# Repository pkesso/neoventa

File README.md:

# Neoventa — Venta Overdrive PCB

A PCB for the Venta Overdrive, a clone of the PE-12 overdrive by Elektronika. The board is 50 × 54 mm, has 2 layers and fits a Hammond 1590N1 (125B) enclosure. SMD parts go on the bottom side and are assembled by JLCPCB. Pots and the wire pads go on the top side and are soldered by hand.

The schematic and the board are generated by Python scripts from a single circuit description (`tools/circuit2.py`). The layout was not drawn by hand in KiCad.

## Status

**Done**
- The schematic was traced from the stripboard layout and checked against the factory schematic of the PE-12 (`pics/moar/1.png`, `2.png`).
- The ngspice simulation gives about ±0.25 V at the output for a 100 mV, 440 Hz input at Volume 50% (see `simulations/`).
- The board is placed and routed by the scripts. The scripts' own DRC (`tools/drc.py`) reports 0 violations.
- The JLCPCB BOM and CPL files are generated (`jlcpcb/`).
- There is a drilling template for the enclosure lid.

**To do**
- Fill the GND zones (press **B** in the PCB editor), then run KiCad's DRC (Inspect → Design Rules Checker).
- Export Gerbers and drill files (File → Fabrication Outputs).
- Check the orientation of the SOIC-8 and the diodes in the JLCPCB assembly preview. The assembly side is **Bottom**.
- Add 3D models for the pots. The footprints in `Venta.pretty/` don't have any yet.

## Repository layout

```
venta_overdrive.kicad_pro     KiCad project
venta_overdrive.kicad_sch     Schematic (generated by tools/gen_sch2.py)
venta_overdrive.kicad_pcb     Board (generated by tools/write_pcb.py)
Venta.kicad_sym               Project symbol library
Venta.pretty/                 Project footprints: Alpha 16 mm RA pots (single/dual), wire pad
fp-lib-table, sym-lib-table   Library tables (paths relative to ${KIPRJMOD})
jlcpcb/                       BOM_JLCPCB.csv, CPL_JLCPCB.csv for JLCPCB assembly
simulations/                  venta.lib (SPICE models), simulate.py and the plots it generates
drill_template_1590N1.pdf     Lid drilling template, print at 100 % scale (generated by tools/drill_template.py)
tools/                        Python scripts that generate the schematic and the board
requirements.txt              Python dependencies for tools/
```

## Hardware

- **Enclosure:** Hammond 1590N1 (66.5 × 122 × 39.5 mm).
- **Knobs:** 2 × 2. Volume and Drive on top, Eq and Resonance below. IN/OUT jacks on the sides, power on the top.
- **Pots:** Alpha 16 mm, right-angle PCB mount ("41" terminals), B50k: RV16AF-41 single, RV16A01F-41 dual for Eq. The footprints follow the [Alpha datasheet](https://cdn-blog.adafruit.com/uploads/2022/01/Taiwan-Alpha-16mm-pots-datasheet.pdf) (pages 43–45): body Ø17, pin rows 16 mm (and 11 mm on the dual) from the shaft, 5 mm pitch.
- **Board height:** the board sits **12 mm** behind the pots' mounting surface (the inside of the lid, where the bushings rest). The dual pot body is 11.5 mm deep (singles 9.1 mm), and the pins are long enough for up to about 13 mm, so all four bushings are flush with the lid only in the 11.5–13 mm window.
- **Op-amps:** 4558 (JRC4558D, LCSC C443686).
- **Footswitch:** 3PDT, wired to the board.
- **Status LED:** external, with its own resistor. Anode to J6 (LED+), cathode to a 3PDT lug; the common of that 3PDT pole goes to J7 (GND), so the LED lights when the effect is on.
- **Wire pads:** J1 IN, J2 OUT, J3 +9V, J4/J5 GND, J6 LED+ (VCC, to the LED anode), J7 GND (to the 3PDT LED pole).

### Power: DC jack or 9 V battery

The board takes power from J3 (+9V) and J4 (GND) and does not care where it comes from. Switching between a 9 V adapter
and a 9 V (PP3) battery is done off the board, with two switching jacks:

- a 2.1 mm DC jack with a switch lug that is connected to the jack's + contact only while no plug is inserted;
- a stereo (TRS) input jack: its ring lug works as the battery switch.

```
battery +        -> DC jack switch lug
DC jack +        -> J3 (+9V)        (Boss-style adapter: centre negative, sleeve positive)
DC jack -        -> J4 (GND)
battery -        -> input jack ring (R)
input jack sleeve (S) -> J5 (GND)
input jack tip (T)    -> 3PDT -> J1 (IN)
```

- Without an adapter, the battery + reaches J3 through the DC jack's switch lug. Plugging the adapter in opens the switch
  lug, so the battery is disconnected and the pedal runs from the adapter.
- A mono guitar cable in the input jack shorts the ring to the sleeve and connects the battery -. Unplugging the cable
  turns the battery off, so the pedal must not be left with a cable plugged in.
- D3 (SS14) protects against reverse polarity for both sources and drops about 0.3–0.4 V.
- Current draw is about 8–12 mA for the three 4558s plus the status LED (2–10 mA depending on its resistor). An
  alkaline PP3 (~500 mAh) lasts roughly 25–50 hours; a dimmer LED (1–2 mA) noticeably extends that.
- The circuit keeps working down to about 6–7 V, but the op-amps start to clip earlier as the battery runs down.
- Space: a PP3 is 48.5 × 26.5 × 17.5 mm and the free depth under the board in the 1590N1 is only about 20 mm, so check
  the battery's place against the footswitch and jacks before drilling.

### Changes from the original circuit
- R8 (filter summer input) is 75 kΩ as in the factory schematic; the stripboard layout has 15 kΩ, which makes the pedal about 13 dB louder with a weaker resonance peak.
- Resonance (RV2) is wired so that turning it clockwise increases the resonance, as on the original; the stripboard layout has it reversed.
- 1N5817 → SS14, 47 µF → 22 µF ceramic, 1.5 MΩ → 1 MΩ (input pull-down).
- Added 3 × 100 nF supply decoupling caps for the op-amps.
- 1.5 nF filter caps are C0G (NP0).

## Simulation

The schematic contains SPICE fields (`Sim.*`) that point to `simulations/venta.lib`. The library has behavioural models of the op-amp, the diodes and the pots. To run a simulation in KiCad, open Inspect → Simulator. The analysis is taken from the `.tran` text on the schematic. Pot positions are set in the `Sim.Params` field of RV1..RV4 (`POS = 0..1`). V1/V2 are simulation-only sources.

The plots in `simulations/` are generated by `simulate.py`:

```bash
.venv/Scripts/python simulations/simulate.py
```

It builds the netlist from `tools/circuit2.py` and runs ngspice as a shared library: the `ngspice.dll` that ships with KiCad 10, found through `KICAD_BIN` (see Tools).

- `sim_frequency.png` — small-signal frequency response for the Eq and Resonance knobs at 0/50/100 %.
- `sim_waveforms.png` — 440 Hz, 100 mV input and the output at Drive 10/50/100 %.

`render_wav.py` runs a recording through the simulated pedal and writes the result to a WAV file:

```bash
.venv/Scripts/python simulations/render_wav.py riff.wav riff_out.wav --drive 80 --eq 30 --res 70 --volume 60
```

- The input should be a dry (DI) guitar recording; the first channel is used. Its peak is scaled to `--peak` volts
  (default 0.2 V, a single coil; humbuckers give more).
- Knobs are in percent, 0–100 (default 50). `--start` and `--duration` cut a fragment, in seconds.
- `--pickup` drives the input through a single-coil pickup and cable model instead of an ideal source.
- The output is 16-bit PCM at the input's sample rate, normalised to −1 dBFS; `--gain` sets a fixed scale instead
  (dBFS per volt), so different settings can be compared by level.
- It runs at roughly real time (about a minute of computation per minute of audio). The op-amp and diode models in
  `venta.lib` are behavioural, so this shows the character of the circuit rather than an exact copy of a real pedal.

## Tools

Python 3 with numpy, scipy and matplotlib:

```bash
python -m venv .venv
.venv/Scripts/pip install -r requirements.txt
```

`gen_sch2.py` and `write_pcb.py` also need KiCad 10: after writing the files they resave them in the KiCad 10 format with `kicad-cli ... upgrade`. The scripts, `tools/check.py` and `simulations/simulate.py` look for KiCad's bin directory (`kicad-cli`, `ngspice.dll`) in this order: the `KICAD_BIN` environment variable, the directory of `kicad-cli` on `PATH`, then the default install `%ProgramFiles%\KiCad\10.0\bin`. With a standard KiCad 10 install on Windows nothing needs to be set.

`tools/verify2.py` also needs the standalone [ngspice](https://ngspice.sourceforge.io) program. It runs ngspice as a separate program, so it can't use KiCad's `ngspice.dll` the way `simulations/simulate.py` does.

Scripts are run from the `tools/` directory. The pipeline:

| Step | Script | Input → output |
|---|---|---|
| Circuit | `circuit2.py` | Single source of truth: parts, nets, footprints, board side, LCSC numbers |
| Initial placement | `render.py` | → `placed.json`, `placement.png` |
| Placement optimisation | `anneal.py` | `placed.json` → `placed2.json` |
| Routing | `run_route.py` (uses `route.py`) | `placed2.json` → `routed.pkl`, `routed.png` |
| DRC | `drc.py` | `routed.pkl` → report |
| Schematic | `gen_sch2.py` | → `.kicad_sch`, `Venta.kicad_sym`, `sym-lib-table`, `symuuid.json` (and `.kicad_pro` only if it is missing) |
| Board | `write_pcb.py` | `routed.pkl`, `symuuid.json` → `.kicad_pcb`, `Venta.pretty/`, `fp-lib-table` |
| Check | `verify2.py <file.kicad_sch>` | Rebuilds connectivity from the schematic, compares it with `circuit2.py`, runs ngspice |
| Drilling template | `drill_template.py` | Hole positions from `place.py` → `../drill_template_1590N1.pdf` (A4, 1:1) |

Helper modules: `check.py` (repository checks, see below), `place.py` (board outline, placement), `route.py` (2-layer A* grid router, 0.25 mm grid; turns cost extra, so tracks run straight with 45° bends), `pcb_core.py` (footprint loading and geometry, reads `tools/fplib/`: copies of the KiCad 10 library footprints used on the board, so the output does not depend on the installed library version), `kicad_cli.py` (runs `kicad-cli upgrade`), `k10fmt.py` (KiCad 10 library formatter, no longer used by the pipeline).

Notes:
- `routed.pkl` is in `.gitignore`. Without it, `write_pcb.py` can only run after routing again.
- `gen_sch2.py` and `write_pcb.py` overwrite the KiCad files. Changes made by hand in KiCad will be lost if you regenerate them.
- The generators are deterministic: running them again on unchanged inputs reproduces the committed files byte for byte.
- `write_pcb.py` copies library footprints whole from `tools/fplib/` and places the silkscreen labels (1.0 mm text) where they clear pads, other silkscreen and the board edge.

## Checks

`tools/check.py` validates the repository. It needs only the Python standard library and `kicad-cli`.

| Check | What it verifies |
|---|---|
| `format` | KiCad files are in KiCad 10 format |
| `paths` | No absolute paths in KiCad files and library tables |
| `english` | No Cyrillic text in the repository's text files |
| `python` | Python scripts compile |
| `erc` | KiCad ERC reports no errors |
| `drc` | KiCad DRC reports no errors (zones are refilled for the check, the board file is not changed; includes schematic parity) |
| `assembly` | `jlcpcb/` BOM and CPL match the board: parts, values, LCSC numbers, position, side, rotation |

```bash
.venv/Scripts/python tools/check.py
```

Run selected checks by name (`tools/check.py drc assembly`). ERC/DRC warnings are listed but only fail with `--strict`. To accept a DRC/ERC item, exclude it in KiCad (right click → Exclude); excluded items are not reported.

The same script runs as a git pre-commit hook. It runs only the checks relevant to the staged files and blocks the commit if any of them fails. Enable it once per clone:

```bash
git config core.hooksPath .githooks
```

The hook checks the working tree, not the staged versions of the files.

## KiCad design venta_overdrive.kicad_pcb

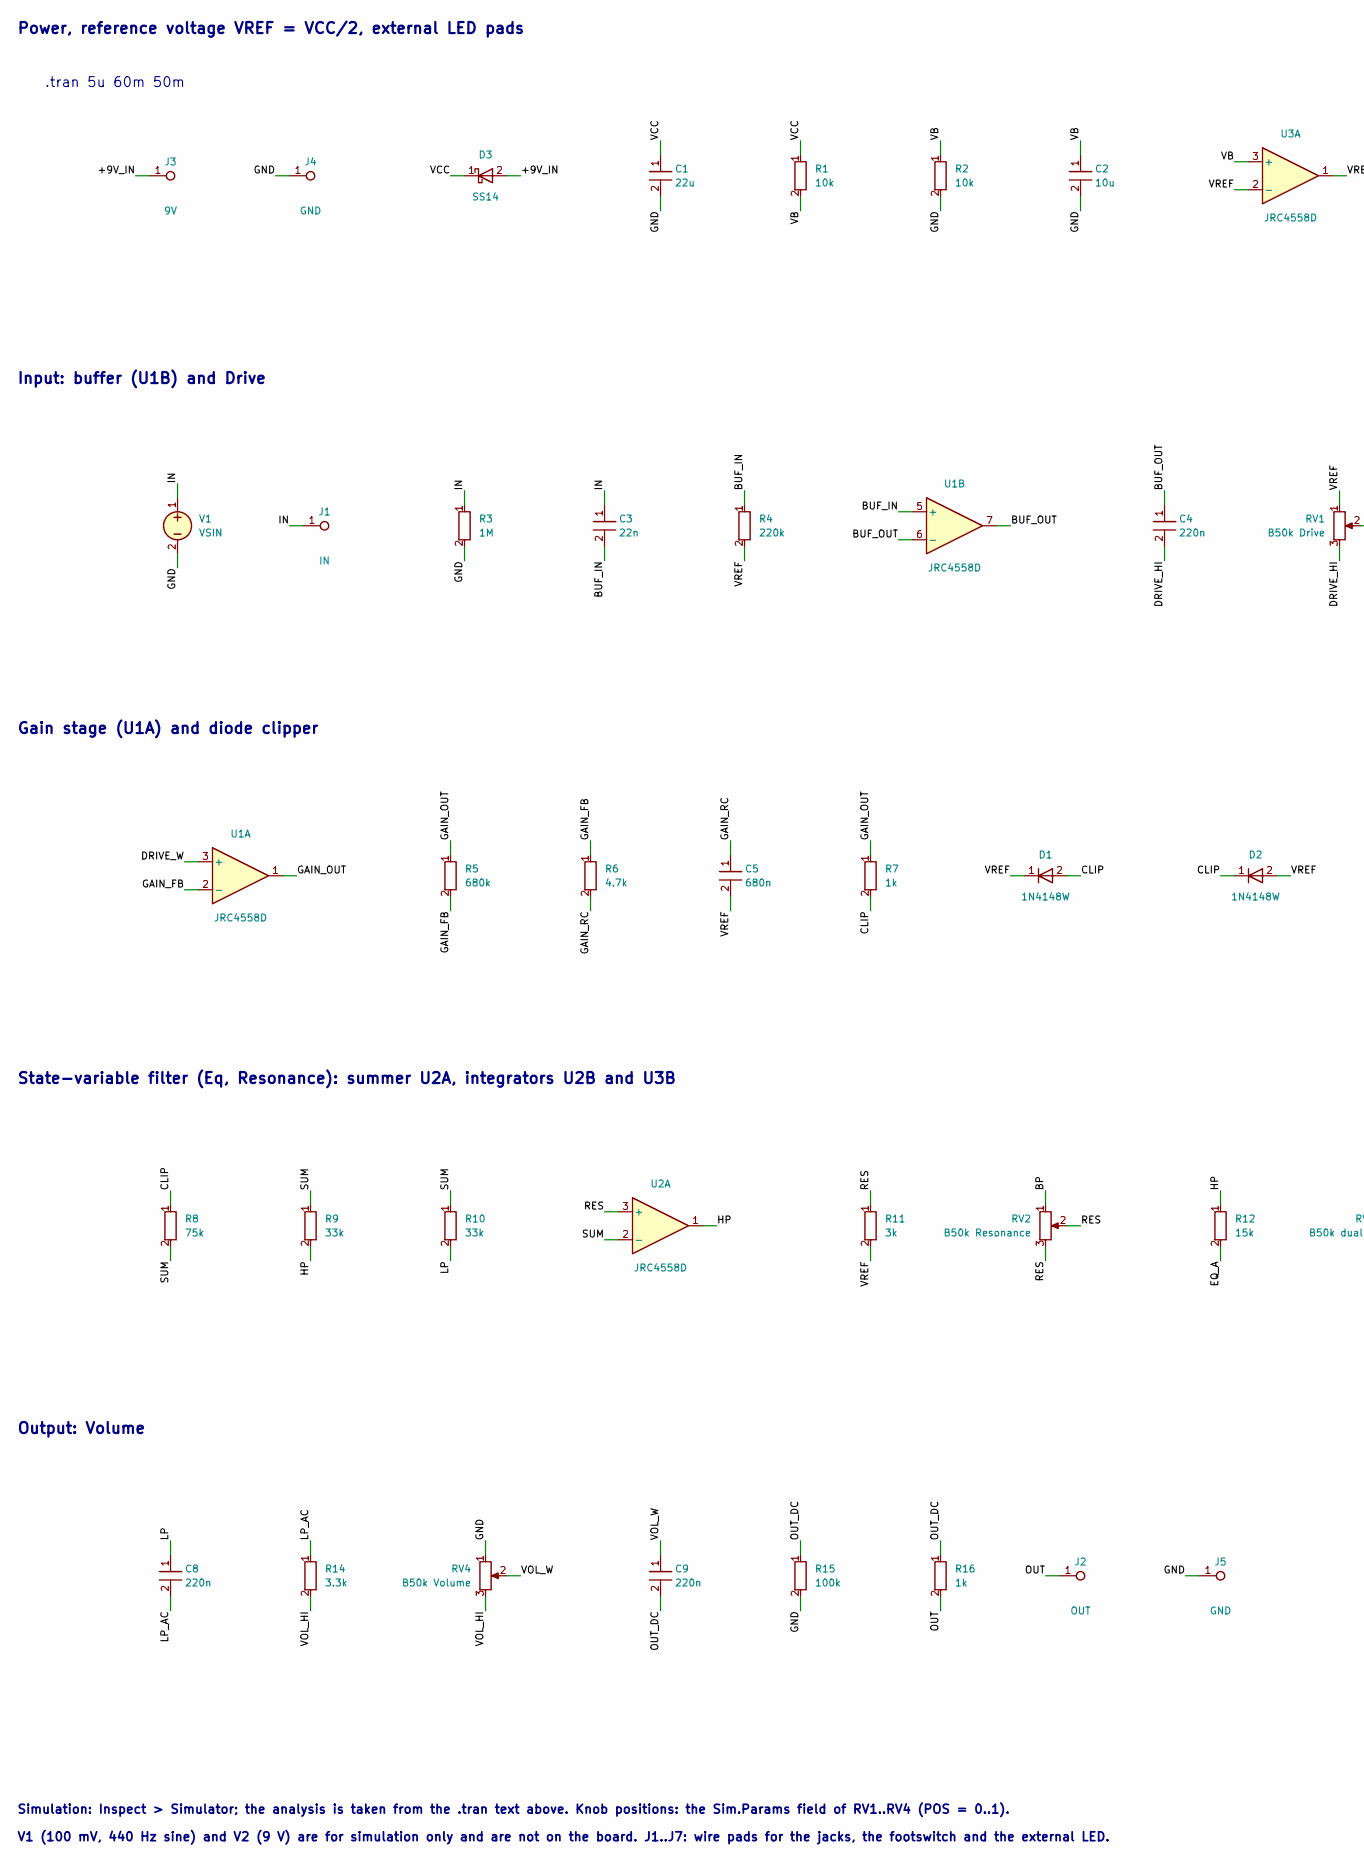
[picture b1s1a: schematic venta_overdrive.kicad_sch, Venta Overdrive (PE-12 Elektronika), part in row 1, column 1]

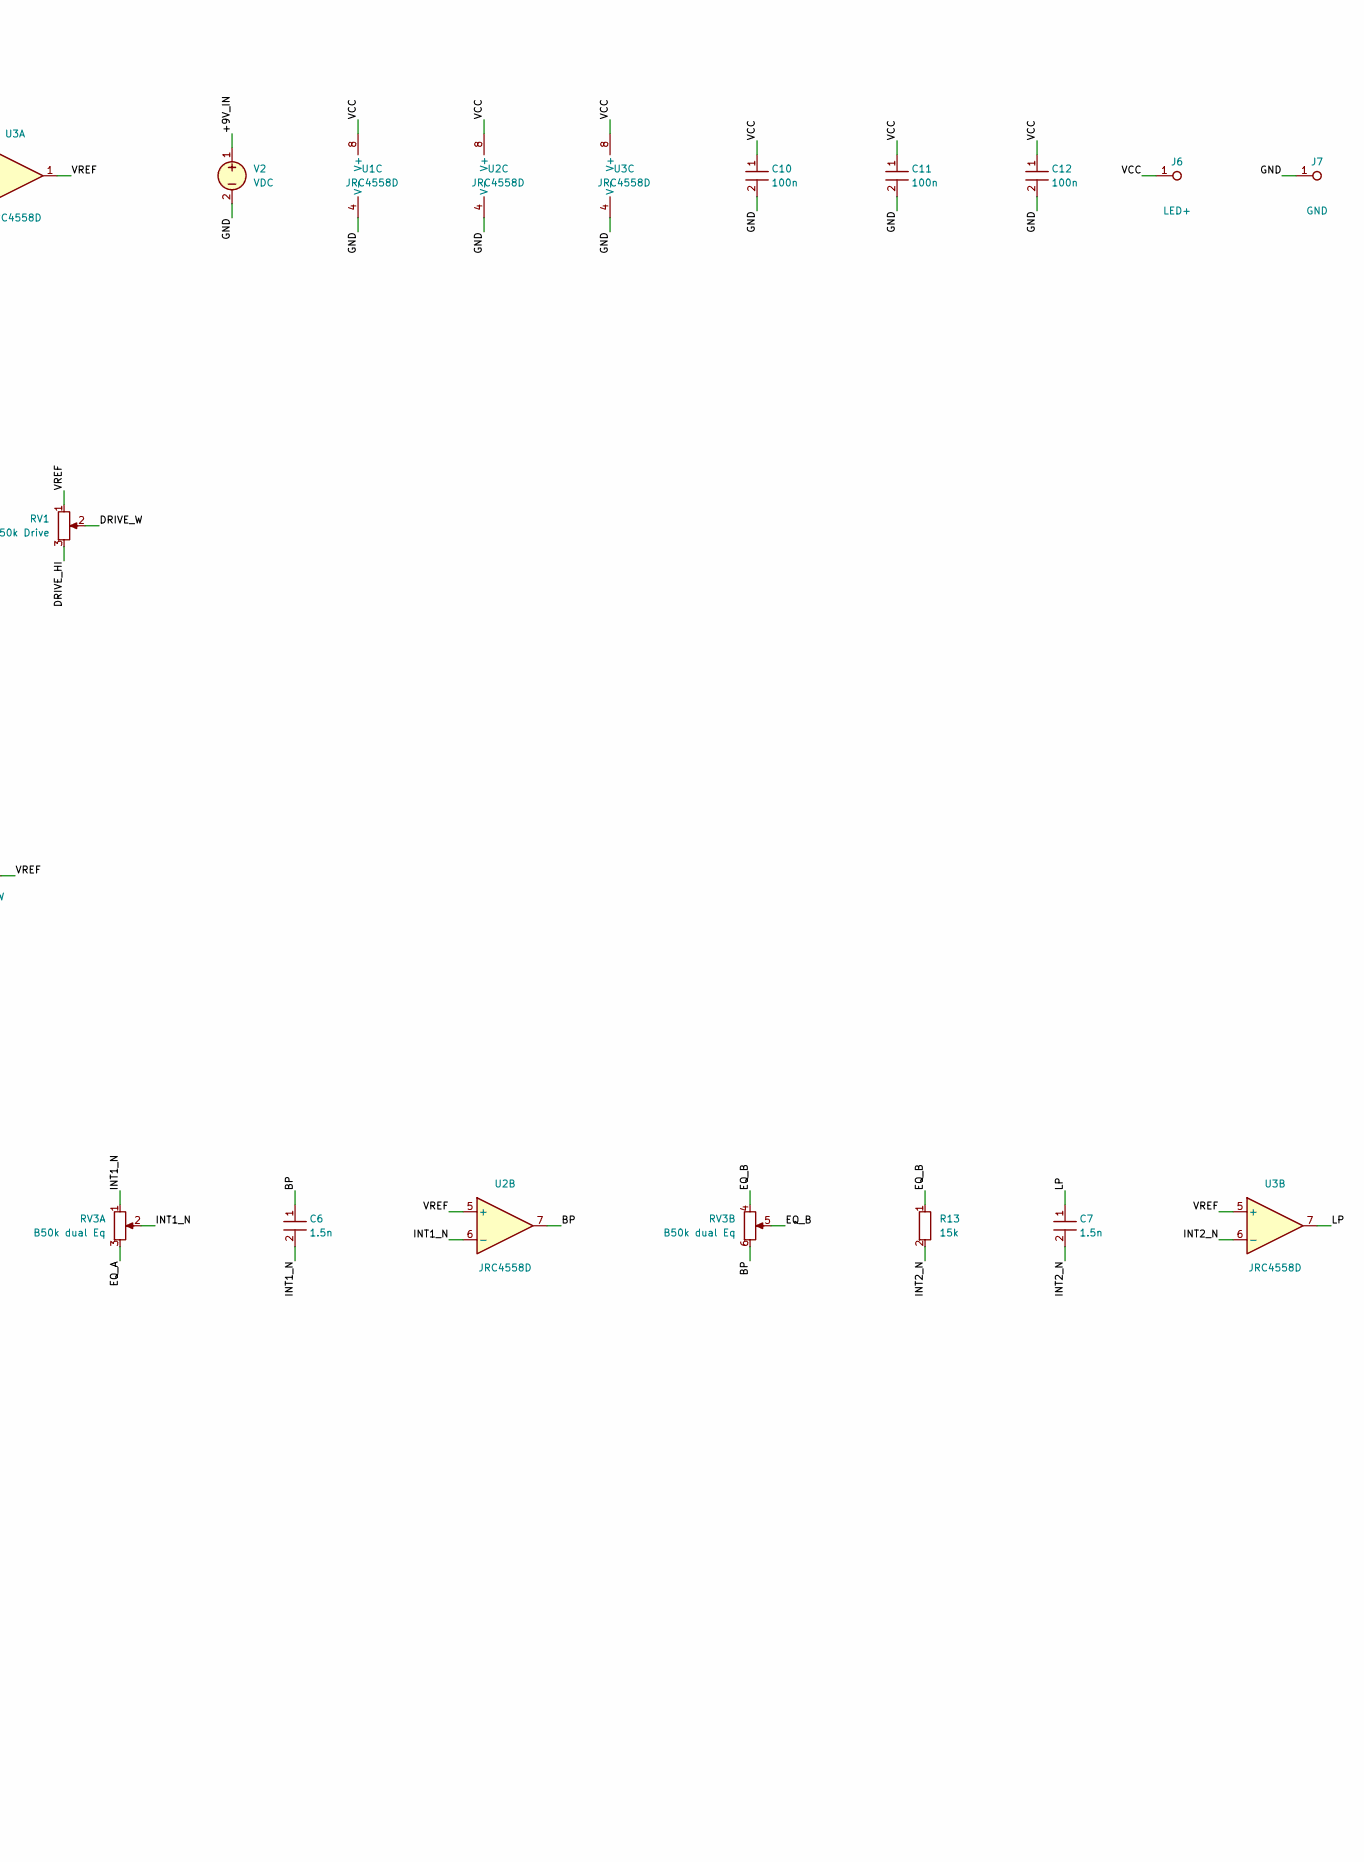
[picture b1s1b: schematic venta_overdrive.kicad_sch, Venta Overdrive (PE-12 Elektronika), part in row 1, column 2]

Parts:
C1: 22u; C_1206_3216Metric; LCSC C12891
C2: 10u; C_0805_2012Metric; LCSC C15850
C3: 22n; C_0805_2012Metric; LCSC C1729
C4, C8, C9: 220n; C_0805_2012Metric; LCSC C5378
C5: 680n; C_0805_2012Metric; LCSC C107133
C6, C7: 1.5n; C_0603_1608Metric; LCSC C107039
C10, C11, C12: 100n; C_0805_2012Metric; LCSC C49678
D1, D2: 1N4148W; D_SOD-123; LCSC C81598
D3: SS14; D_SMA; LCSC C2480
J1: IN; WirePad
J2: OUT; WirePad
J3: 9V; WirePad
J4, J5, J7: GND; WirePad
J6: LED+; WirePad
R1, R2: 10k; R_0805_2012Metric; LCSC C17414
R3: 1M; R_0805_2012Metric; LCSC C17514
R4: 220k; R_0805_2012Metric; LCSC C17556
R5: 680k; R_0805_2012Metric; LCSC C17797
R6: 4.7k; R_0805_2012Metric; LCSC C17673
R7, R16: 1k; R_0805_2012Metric; LCSC C17513
R8: 75k; R_0805_2012Metric; LCSC C17819
R9, R10: 33k; R_0805_2012Metric; LCSC C17633
R11: 3k; R_0805_2012Metric; LCSC C17661
R12, R13: 15k; R_0805_2012Metric; LCSC C17475
R14: 3.3k; R_0805_2012Metric; LCSC C26010
R15: 100k; R_0805_2012Metric; LCSC C149504
RV1: B50k Drive; Pot_Alpha_16mm_RA_Single
RV2: B50k Resonance; Pot_Alpha_16mm_RA_Single
RV3: B50k dual Eq; Pot_Alpha_16mm_RA_Dual
RV4: B50k Volume; Pot_Alpha_16mm_RA_Single
U1, U2, U3: JRC4558D; SOIC-8_3.9x4.9mm_P1.27mm; LCSC C443686
V1: VSIN
V2: VDC

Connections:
/+9V_IN: D3.2 (A), J3.1, V2.1 (+)
/BP: C6.1, RV2.1, RV3.6, U2.7
/BUF_IN: C3.2, R4.1, U1.5 (+)
/BUF_OUT: C4.1, U1.6 (-), U1.7
/CLIP: D1.2 (A), D2.1 (K), R7.2, R8.1
/DRIVE_HI: C4.2, RV1.3
/DRIVE_W: RV1.2, U1.3 (+)
/EQ_A: R12.2, RV3.3
/EQ_B: R13.1, RV3.4, RV3.5
/GAIN_FB: R5.2, R6.1, U1.2 (-)
/GAIN_OUT: R5.1, R7.1, U1.1
/GAIN_RC: C5.1, R6.2
/GND: C1.2, C2.2, C10.2, C11.2, C12.2, J4.1, J5.1, J7.1, R2.2, R3.2, R15.2, RV4.1, U1.4 (V-), U2.4 (V-), U3.4 (V-), V1.2 (-), V2.2 (-)
/HP: R9.2, R12.1, U2.1
/IN: C3.1, J1.1, R3.1, V1.1 (+)
/INT1_N: C6.2, RV3.1, RV3.2, U2.6 (-)
/INT2_N: C7.2, R13.2, U3.6 (-)
/LP: C7.1, C8.1, R10.2, U3.7
/LP_AC: C8.2, R14.1
/OUT: J2.1, R16.2
/OUT_DC: C9.2, R15.1, R16.1
/RES: R11.1, RV2.2, RV2.3, U2.3 (+)
/SUM: R8.2, R9.1, R10.1, U2.2 (-)
/VB: C2.1, R1.2, R2.1, U3.3 (+)
/VCC: C1.1, C10.1, C11.1, C12.1, D3.1 (K), J6.1, R1.1, U1.8 (V+), U2.8 (V+), U3.8 (V+)
/VOL_HI: R14.2, RV4.3
/VOL_W: C9.1, RV4.2
/VREF: C5.2, D1.1 (K), D2.2 (A), R4.2, R11.2, RV1.1, U2.5 (+), U3.1, U3.2 (-), U3.5 (+)

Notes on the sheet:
.tran 5u 60m 50m
Power, reference voltage VREF = VCC/2, external LED pads
Output: Volume
V1 (100 mV, 440 Hz sine) and V2 (9 V) are for simulation only and are not on the board. J1..J7: wire pads for the jacks, the footswitch and the external LED.
Input: buffer (U1B) and Drive
Simulation: Inspect > Simulator; the analysis is taken from the .tran text above. Knob positions: the Sim.Params field of RV1..RV4 (POS = 0..1).
Gain stage (U1A) and diode clipper
State-variable filter (Eq, Resonance): summer U2A, integrators U2B and U3B

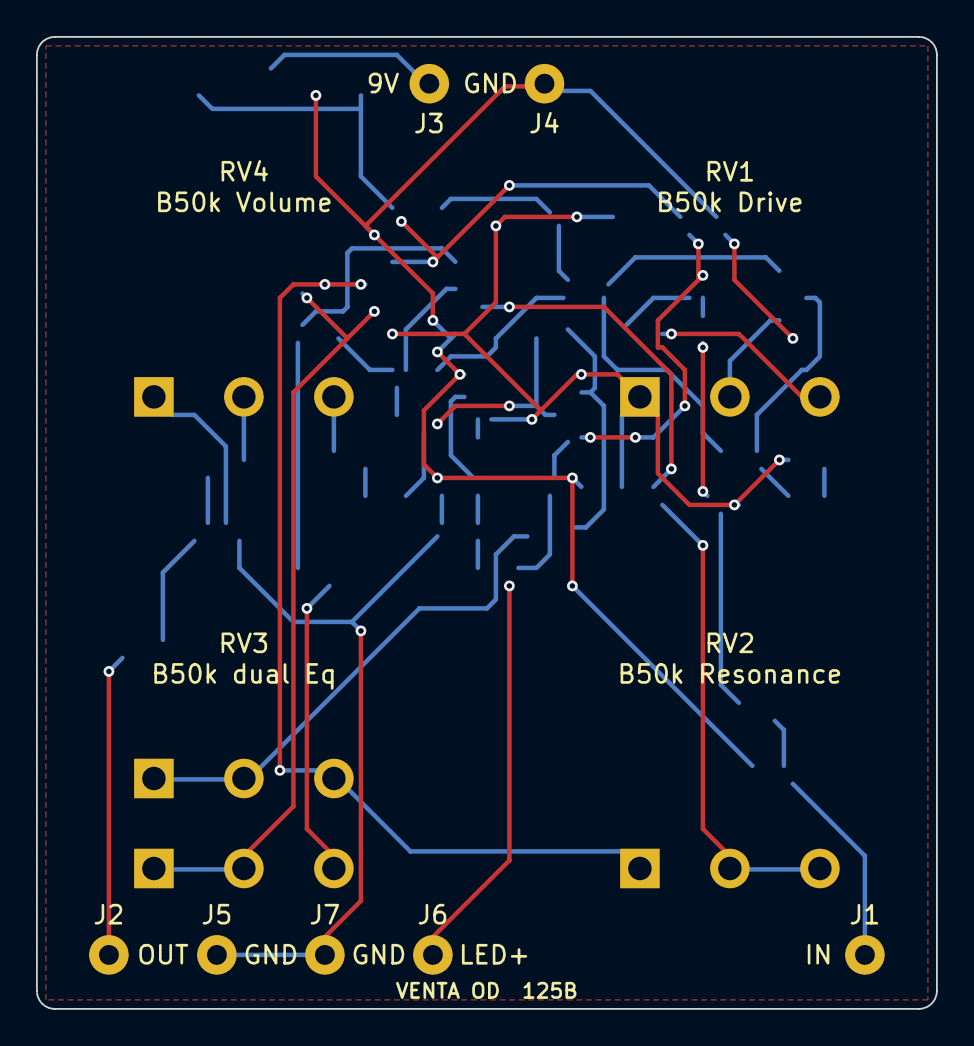
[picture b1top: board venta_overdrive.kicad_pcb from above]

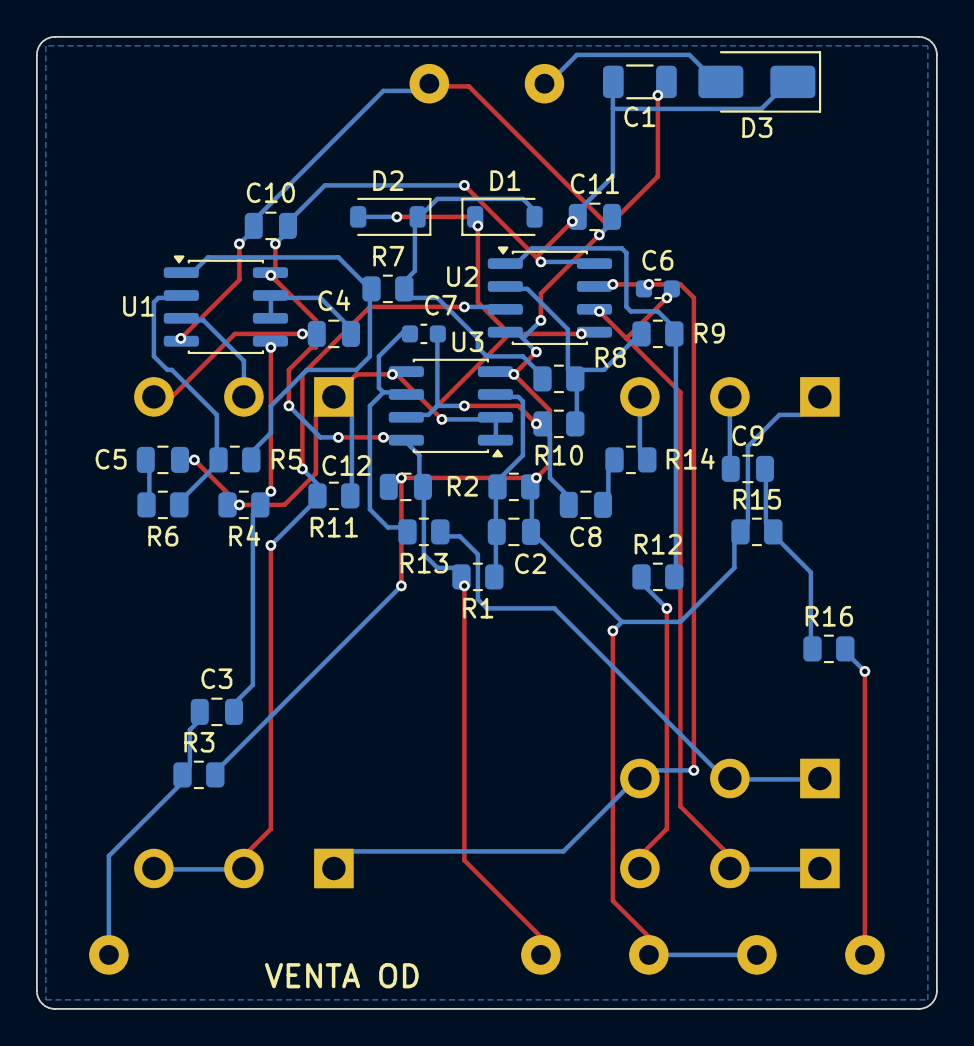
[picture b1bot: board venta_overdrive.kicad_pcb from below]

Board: 2 copper layers, 50.0 x 54.0 mm, 45 parts (34 on the bottom side), 28 nets.

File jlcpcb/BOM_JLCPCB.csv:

Comment,Designator,Footprint,LCSC Part #
22u,C1,1206,C12891
100n,"C10,C11,C12",0805,C49678
10u,C2,0805,C15850
22n,C3,0805,C1729
220n,"C4,C8,C9",0805,C5378
680n,C5,0805,C107133
1.5n,"C6,C7",0603,C107039
1N4148W,"D1,D2",SOD-123,C81598
SS14,D3,SMA,C2480
10k,"R1,R2",0805,C17414
3k,R11,0805,C17661
3.3k,R14,0805,C26010
100k,R15,0805,C149504
1M,R3,0805,C17514
220k,R4,0805,C17556
680k,R5,0805,C17797
4.7k,R6,0805,C17673
1k,"R7,R16",0805,C17513
15k,"R12,R13",0805,C17475
75k,R8,0805,C17819
33k,"R9,R10",0805,C17633
JRC4558D,"U1,U2,U3",SOIC-8,C443686
